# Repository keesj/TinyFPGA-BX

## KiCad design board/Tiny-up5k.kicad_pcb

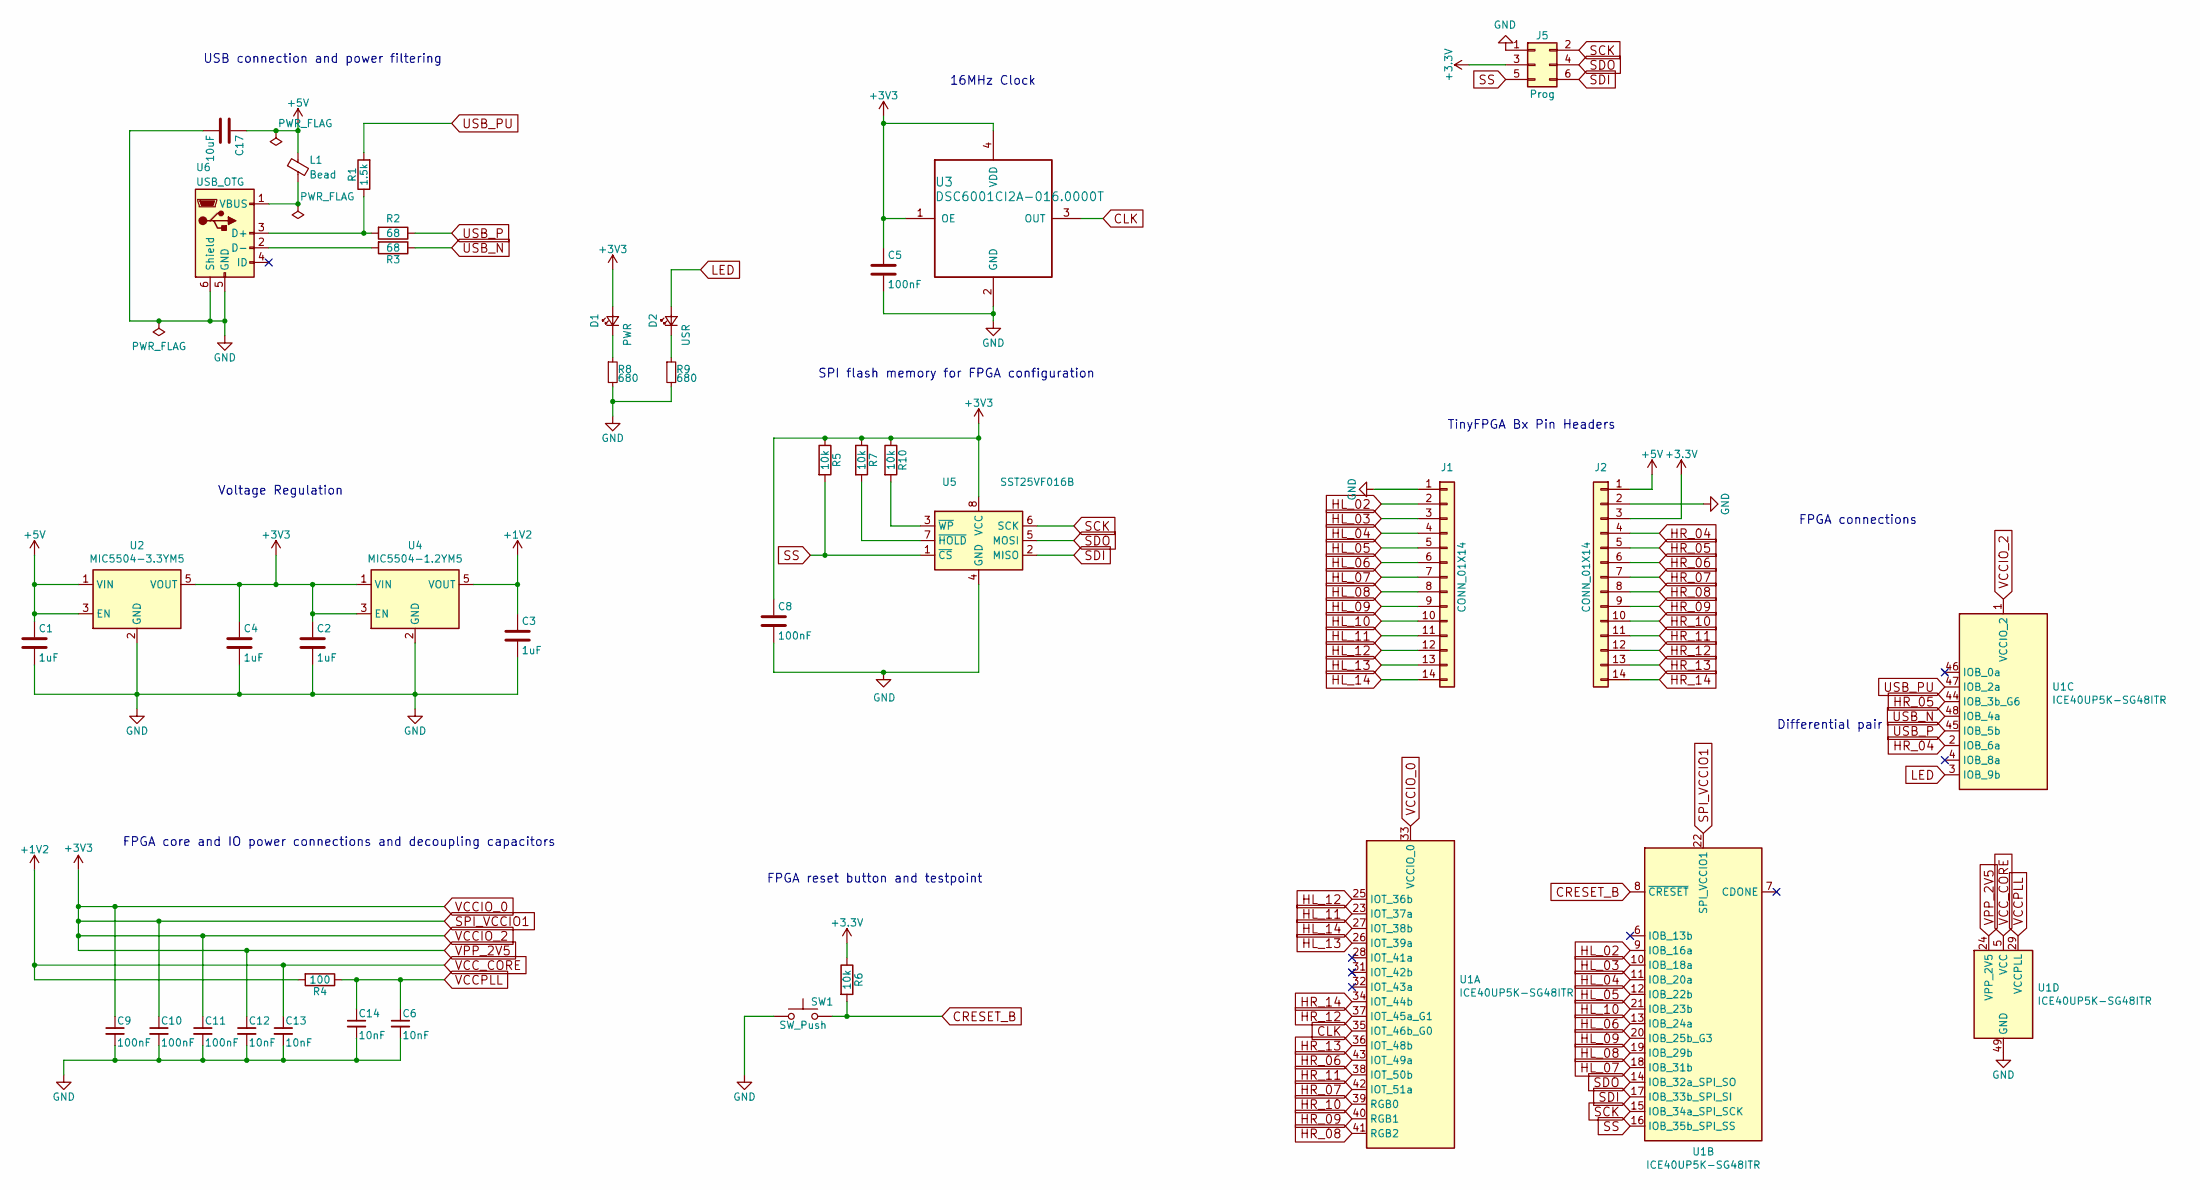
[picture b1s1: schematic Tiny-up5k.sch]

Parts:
C1, C2, C3, C4: 1uF; C_0402_1005Metric
C5, C8, C9, C10, C11: 100nF; C_0402_1005Metric
C6, C12, C13, C14: 10nF; C_0402_1005Metric
C17: 10uF; C_0603_1608Metric
D1: PWR; LED_0402_1005Metric
D2: USR; LED_0402_1005Metric
J1, J2: CONN_01X14; Pin_Header_Straight_1x14_Pitch2.54mm
J5: Prog; PinHeader_2x03_P2.54mm_Vertical_SMD_NoSolder
L1: Bead; L_0603
R1: 1.5k; R_0402_1005Metric
R2, R3: 68; R_0402_1005Metric
R4: 100; R_0402_1005Metric
R5, R6, R7, R10: 10k; R_0402_1005Metric
R8, R9: 680; R_0402_1005Metric
SW1: SW_Push; SW_SPST_B3U-1000P
U1: ICE40UP5K-SG48ITR; QFN-48-1EP_7x7mm_P0.5mm_EP5.15x5.15mm
U2: MIC5504-3.3YM5; SOT-23-5
U3: DSC6001CI2A-016.0000T; Oscillator_SMD_EuroQuartz_XO32-4Pin_3.2x2.5mm
U4: MIC5504-1.2YM5; SOT-23-5
U5: SST25VF016B; WSON-8-1EP_6x5mm_P1.27mm_EP3.4x4mm
U6: USB_OTG; USB_Micro-B_GCT_USB3076-30-A

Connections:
+5V: C1.1, C17.1, J2.1, L1.1, U2.1 (VIN), U2.3 (EN)
CLK: U1.35 (IOT_46b_G0), U3.3 (OUT)
CRESET_B: R6.2, SW1.2, U1.8 (~CRESET)
GND: C1.2, C2.2, C3.2, C4.2, C5.2, C6.2, C8.2, C9.2, C10.2, C11.2, C12.2, C13.2, C14.2, C17.2, J1.1, J2.2, J5.1, R8.2, R9.2, SW1.1, U1.49 (GND), U2.2 (GND), U3.2 (GND), U4.2 (GND), U5.4 (GND), U5.9 (GND), U6.5 (GND), U6.6 (Shield)
HL_02: J1.2, U1.9 (IOB_16a)
HL_03: J1.3, U1.10 (IOB_18a)
HL_04: J1.4, U1.11 (IOB_20a)
HL_05: J1.5, U1.12 (IOB_22b)
HL_06: J1.6, U1.13 (IOB_24a)
HL_07: J1.7, U1.18 (IOB_31b)
HL_08: J1.8, U1.19 (IOB_29b)
HL_09: J1.9, U1.20 (IOB_25b_G3)
HL_10: J1.10, U1.21 (IOB_23b)
HL_11: J1.11, U1.23 (IOT_37a)
HL_12: J1.12, U1.25 (IOT_36b)
HL_13: J1.13, U1.26 (IOT_39a)
HL_14: J1.14, U1.27 (IOT_38b)
HR_04: J2.4, U1.2 (IOB_6a)
HR_05: J2.5, U1.44 (IOB_3b_G6)
HR_06: J2.6, U1.43 (IOT_49a)
HR_07: J2.7, U1.42 (IOT_51a)
HR_08: J2.8, U1.41 (RGB2)
HR_09: J2.9, U1.40 (RGB1)
HR_10: J2.10, U1.39 (RGB0)
HR_11: J2.11, U1.38 (IOT_50b)
HR_12: J2.12, U1.37 (IOT_45a_G1)
HR_13: J2.13, U1.36 (IOT_48b)
HR_14: J2.14, U1.34 (IOT_44b)
LED: D2.2 (A), U1.3 (IOB_9b)
unnamed: D1.1 (K), R8.1
unnamed: D2.1 (K), R9.1
unnamed: L1.2, U6.1 (VBUS)
unnamed: R1.1, R2.2, U6.3 (D+)
unnamed: R3.2, U6.2 (D-)
unnamed: R7.2, U5.7 (~HOLD)
unnamed: R10.2, U5.3 (~WP)
SCK: J5.2, U1.15 (IOB_34a_SPI_SCK), U5.6 (SCK)
SDI: J5.6, U1.17 (IOB_33b_SPI_SI), U5.2 (MISO)
SDO: J5.4, U1.14 (IOB_32a_SPI_SO), U5.5 (MOSI)
SS: J5.5, R5.2, U1.16 (IOB_35b_SPI_SS), U5.1 (~CS)
USB_N: R3.1, U1.48 (IOB_4a)
USB_P: R2.1, U1.45 (IOB_5b)
USB_PU: R1.2, U1.47 (IOB_2a)
VCCPLL: C6.1, C14.1, R4.1, U1.29 (VCCPLL)
VCC_CORE: C3.1, C13.1, R4.2, U1.5 (VCC), U1.30 (VCC), U4.5 (VOUT)

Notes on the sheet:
FPGA core and IO power connections and decoupling capacitors
USB connection and power filtering
Voltage Regulation
16MHz Clock
SPI flash memory for FPGA configuration
FPGA reset button and testpoint
FPGA connections
TinyFPGA Bx Pin Headers
Differential pair

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
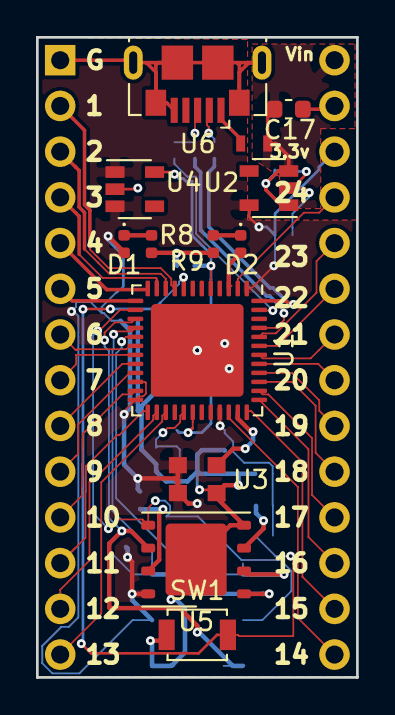
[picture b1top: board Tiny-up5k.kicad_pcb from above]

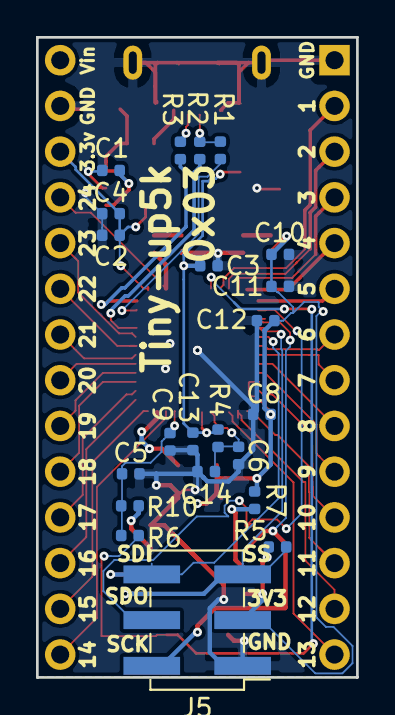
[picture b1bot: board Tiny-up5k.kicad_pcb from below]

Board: 2 copper layers, 17.8 x 35.6 mm, 37 parts (22 on the bottom side), 46 nets.

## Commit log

2018-10-11 After opening in kicad5
2018-10-11 Update to the boards (removed old fpga)
2018-10-12 Moving components around (replaced a few with standard model).
    Also moved resitors and capacitors to the bottom layer
2018-10-15 Cleanup (moving components for better layout)
2018-10-16 Removed a few more pins (SPI FLASH).
    This is the first PCB that passes DRC and has two layers
2018-10-16 add new schematics
2018-10-16 Adding production zip file
2018-10-17 Checked more footprints moves some pads around.
2018-10-17 Cleanup before rename
2018-10-17 Remove pdf
2018-10-17 Rename complete
2018-10-17 Rename "complete"
2018-10-18 Added more part numbers for the components. Changed the footprint of 5v capacitor (make it bigger) to accomodate for the bigger value.
2018-10-18 0x01
2018-11-07 Fix spi flash layout size
2018-11-09 Increase the spacing between the leds and their resistor.
2018-11-10 change j5 footprint for default kicad footprint
2018-11-10 Improve the frabrication layout. Make some trace wider
2018-11-14 Replaced footprint of spi flash chip
2018-11-14 Also fix SMD pad that should get no solder
2018-11-21 Fix SPI line and send rev03 to aisler
2019-03-04 Add Interactive bom
    clone https://github.com/openscopeproject/InteractiveHtmlBom.git
    python2 ~/projects/github/InteractiveHtmlBom/InteractiveHtmlBom/generate_interactive_bom.py Tiny-up5k.kicad_pcb
2019-04-15 Working on a working example
2019-04-16 Add blinky for up5k
2019-04-17 This code is properly working on the board
    tested using
    make -> flash.sh
    and
    apio build -> flash.sh (flash.sh needs editing to select the correct .bin file)
2019-04-18 fix schematics (thanks to mnemonix)
